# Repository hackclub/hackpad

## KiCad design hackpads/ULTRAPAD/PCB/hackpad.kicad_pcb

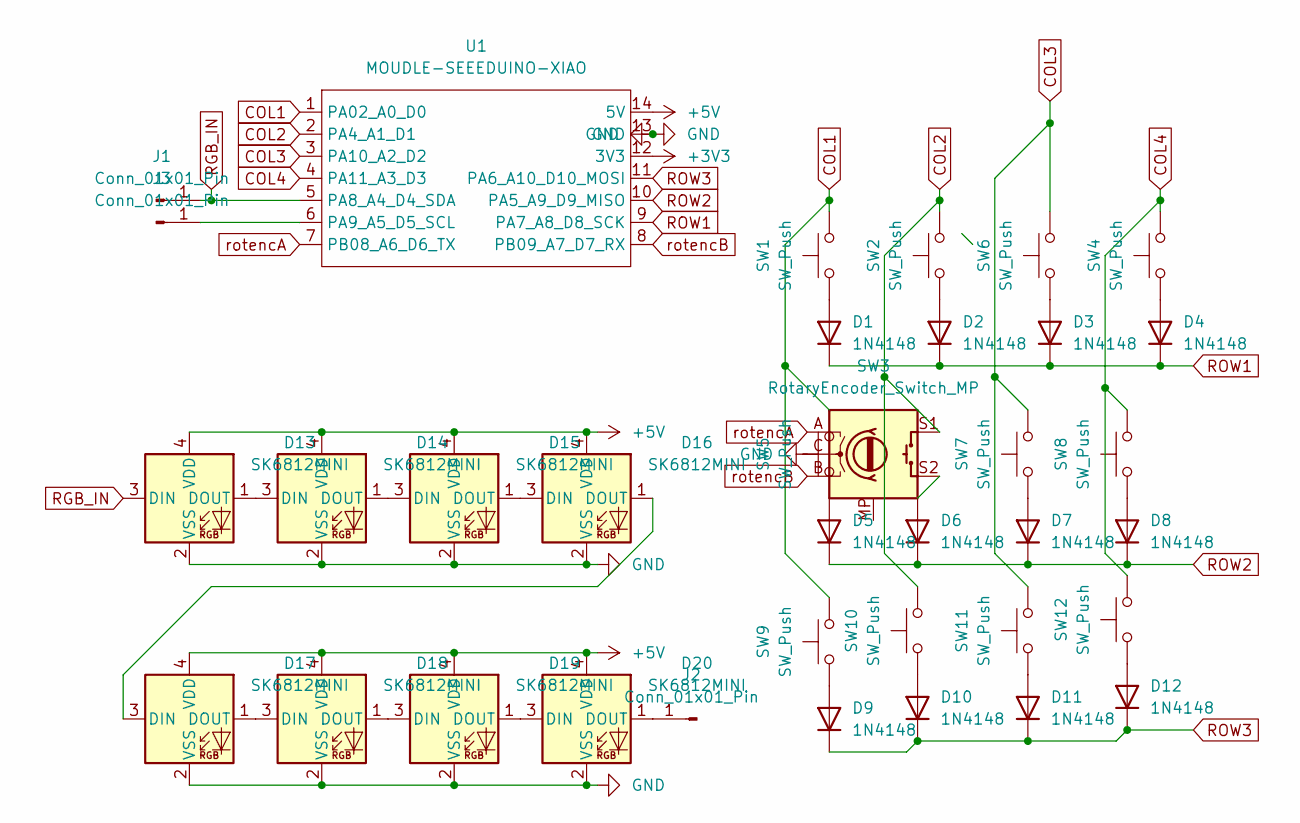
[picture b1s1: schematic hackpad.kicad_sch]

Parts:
D1, D2, D3, D4, D5, D6, D7, D8, D9, D10, D11, D12: 1N4148; D_DO-35_SOD27_P7.62mm_Horizontal
D13, D14, D15, D16, D17, D18, D19, D20: SK6812MINI; LED_SK6812MINI_PLCC4_3.5x3.5mm_P1.75mm
J1, J2, J3: Conn_01x01_Pin; PinHeader_1x01_P1.00mm_Vertical
SW1, SW2, SW4, SW5, SW6, SW7, SW8, SW9, SW10, SW11, SW12: SW_Push; SW_Cherry_MX_1.00u_PCB
SW3: RotaryEncoder_Switch_MP; RotaryEncoder_Alps_EC11E-Switch_Vertical_H20mm
U1: MOUDLE-SEEEDUINO-XIAO; XIAO-RP2040-DIP

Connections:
+3V3: U1.12 (3V3)
+5V: D13.4 (VDD), D14.4 (VDD), D15.4 (VDD), D16.4 (VDD), D17.4 (VDD), D18.4 (VDD), D19.4 (VDD), D20.4 (VDD), U1.14 (5V)
COL1: SW1.2, SW5.2, SW9.2, U1.1 (PA02_A0_D0)
COL2: SW2.2, SW3.S1, SW10.2, U1.2 (PA4_A1_D1)
COL3: SW6.2, SW7.2, SW11.2, U1.3 (PA10_A2_D2)
COL4: SW4.2, SW8.2, SW12.2, U1.4 (PA11_A3_D3)
GND: D13.2 (VSS), D14.2 (VSS), D15.2 (VSS), D16.2 (VSS), D17.2 (VSS), D18.2 (VSS), D19.2 (VSS), D20.2 (VSS), SW3.C, U1.13 (GND)
unnamed: D1.2 (A), SW1.1
unnamed: D2.2 (A), SW2.1
unnamed: D3.2 (A), SW6.1
unnamed: D4.2 (A), SW4.1
unnamed: D5.2 (A), SW5.1
unnamed: D6.2 (A), SW3.S2
unnamed: D7.2 (A), SW7.1
unnamed: D8.2 (A), SW8.1
unnamed: D9.2 (A), SW9.1
unnamed: D10.2 (A), SW10.1
unnamed: D11.2 (A), SW11.1
unnamed: D12.2 (A), SW12.1
unnamed: D13.1 (DOUT), D14.3 (DIN)
unnamed: D14.1 (DOUT), D15.3 (DIN)
unnamed: D15.1 (DOUT), D16.3 (DIN)
unnamed: D16.1 (DOUT), D17.3 (DIN)
unnamed: D17.1 (DOUT), D18.3 (DIN)
unnamed: D18.1 (DOUT), D19.3 (DIN)
unnamed: D19.1 (DOUT), D20.3 (DIN)
unnamed: D20.1 (DOUT), J2.1
unnamed: J3.1, U1.6 (PA9_A5_D5_SCL)
RGB_IN: D13.3 (DIN), J1.1, U1.5 (PA8_A4_D4_SDA)
ROW1: D1.1 (K), D2.1 (K), D3.1 (K), D4.1 (K), U1.9 (PA7_A8_D8_SCK)
ROW2: D5.1 (K), D6.1 (K), D7.1 (K), D8.1 (K), U1.10 (PA5_A9_D9_MISO)
ROW3: D9.1 (K), D10.1 (K), D11.1 (K), D12.1 (K), U1.11 (PA6_A10_D10_MOSI)
rotencA: SW3.A, U1.7 (PB08_A6_D6_TX)
rotencB: SW3.B, U1.8 (PB09_A7_D7_RX)

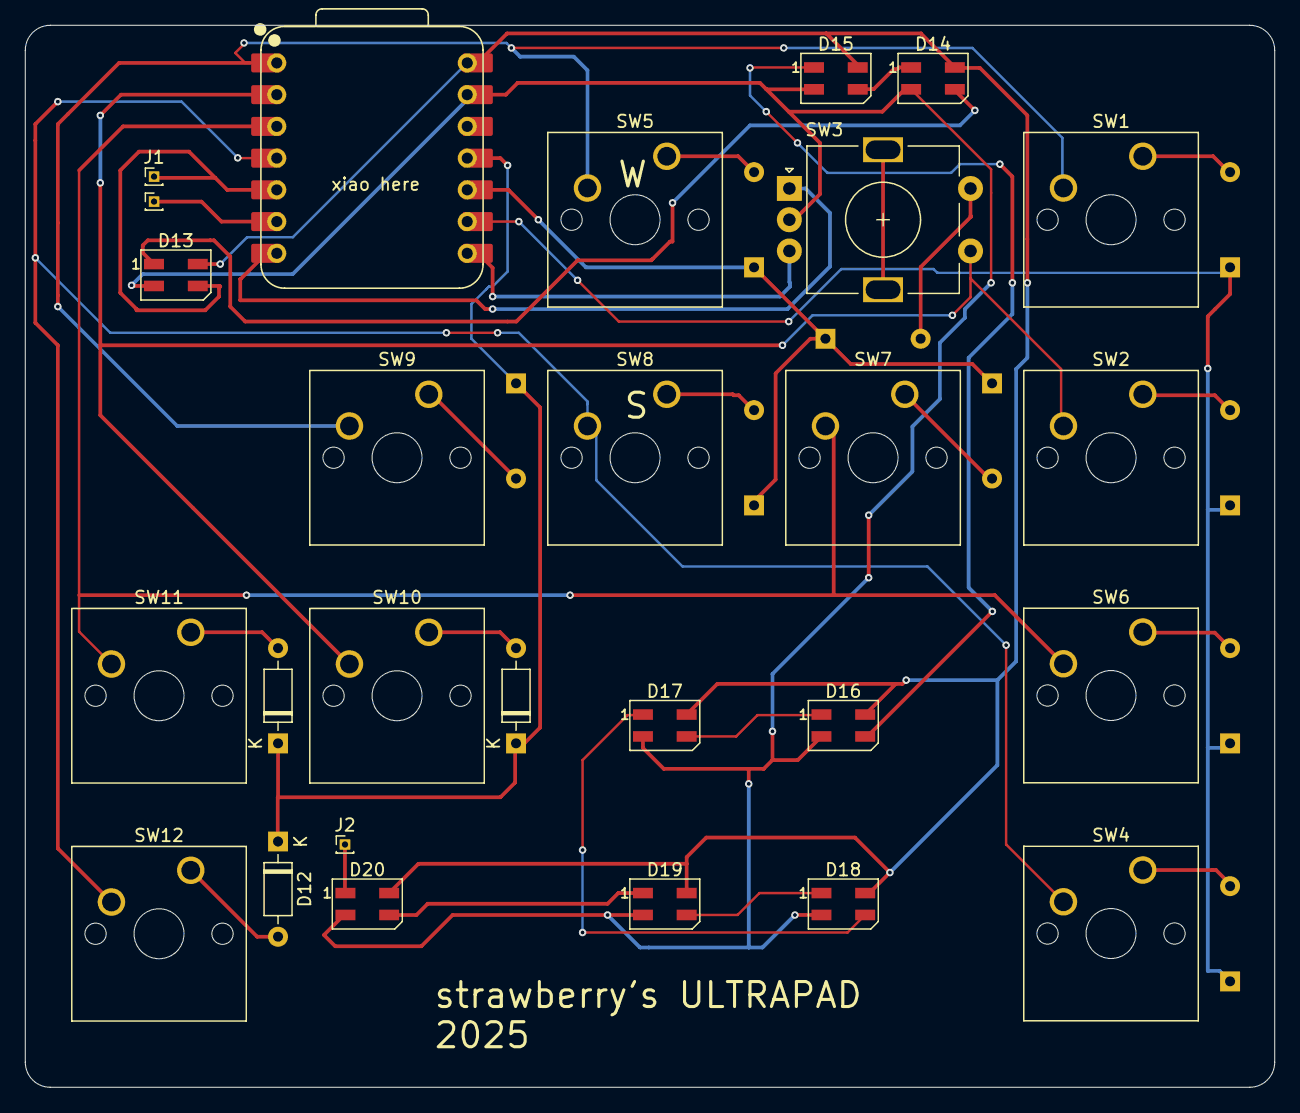
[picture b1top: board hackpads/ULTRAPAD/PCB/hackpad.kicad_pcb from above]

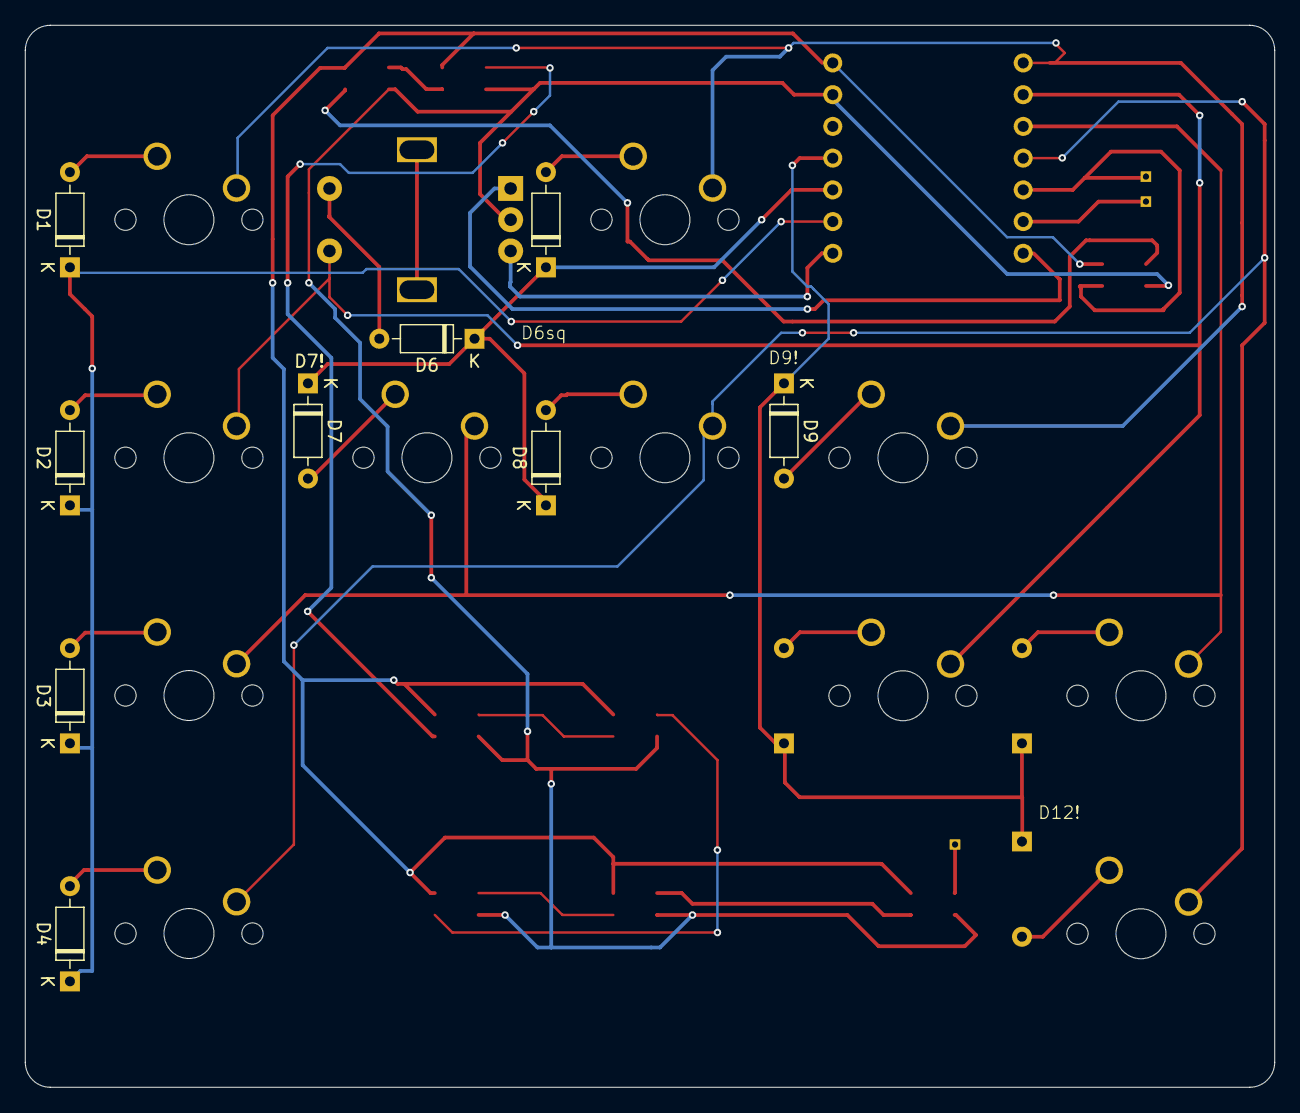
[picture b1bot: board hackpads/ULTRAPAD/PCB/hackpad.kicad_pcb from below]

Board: 2 copper layers, 100.0 x 85.0 mm, 36 parts (9 on the bottom side), 33 nets.

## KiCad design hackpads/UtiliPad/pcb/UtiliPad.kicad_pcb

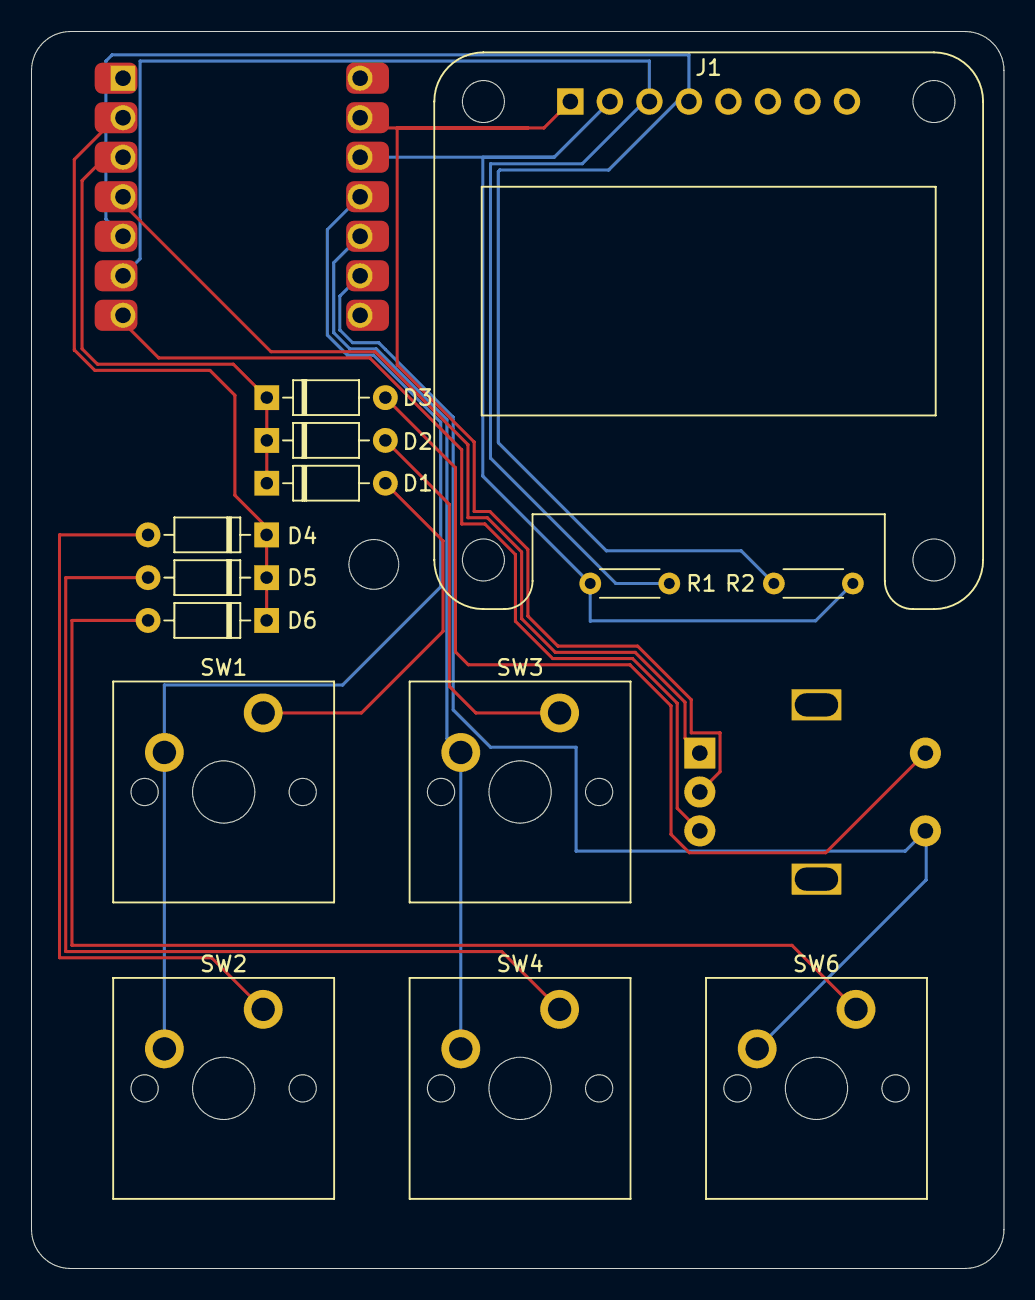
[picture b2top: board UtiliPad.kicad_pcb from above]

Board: 2 copper layers, 62.5 x 79.5 mm, 16 parts (0 on the bottom side), 17 nets.

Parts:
D1, D2, D3, D4, D5, D6: 1N4148; D_DO-35_SOD27_P7.62mm_Horizontal
J1: 0.96" OLED Display; Adafruit_SSD1306
R1, R2: 4.7k; R_Axial_DIN0204_L3.6mm_D1.6mm_P5.08mm_Horizontal
SW1, SW2, SW3, SW4, SW6: MX; MX_PCB_1.00u
SW7: RotaryEncoder_Switch; Encoder_EC11_MX
U1: MCU_Seeed_XIAO_RP2040; Seeed_XIAO_RP2040

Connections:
+3.3V: J1.2, R1.2, R2.2, U1.12 (3V3)
COL0: SW1.1, SW2.1, U1.11 (PA6_A10_D10_MOSI)
COL1: SW3.1, SW4.1, U1.10 (PA5_A9_D9_MISO)
COL2: SW6.1, SW7.S1, U1.9 (PA7_A8_D8_SCK)
GND: J1.1, SW7.C, U1.13 (GND)
unnamed: D1.2 (A), SW1.2
unnamed: D2.2 (A), SW3.2
unnamed: D4.2 (A), SW2.2
unnamed: D5.2 (A), SW4.2
unnamed: D6.2 (A), SW6.2
R1_A: SW7.A, U1.4 (PA11_A3_D3)
R1_B: SW7.B, U1.7 (PB08_A6_D6_TX)
R1_G: D3.2 (A), SW7.S2
ROW0: D1.1 (K), D2.1 (K), D3.1 (K), U1.3 (PA10_A2_D2)
ROW1: D4.1 (K), D5.1 (K), D6.1 (K), U1.2 (PA4_A1_D1)
SCL: J1.3, R1.1, U1.6 (PA9_A5_D5_SCL)
SDA: J1.4, R2.1, U1.5 (PA8_A4_D4_SDA)

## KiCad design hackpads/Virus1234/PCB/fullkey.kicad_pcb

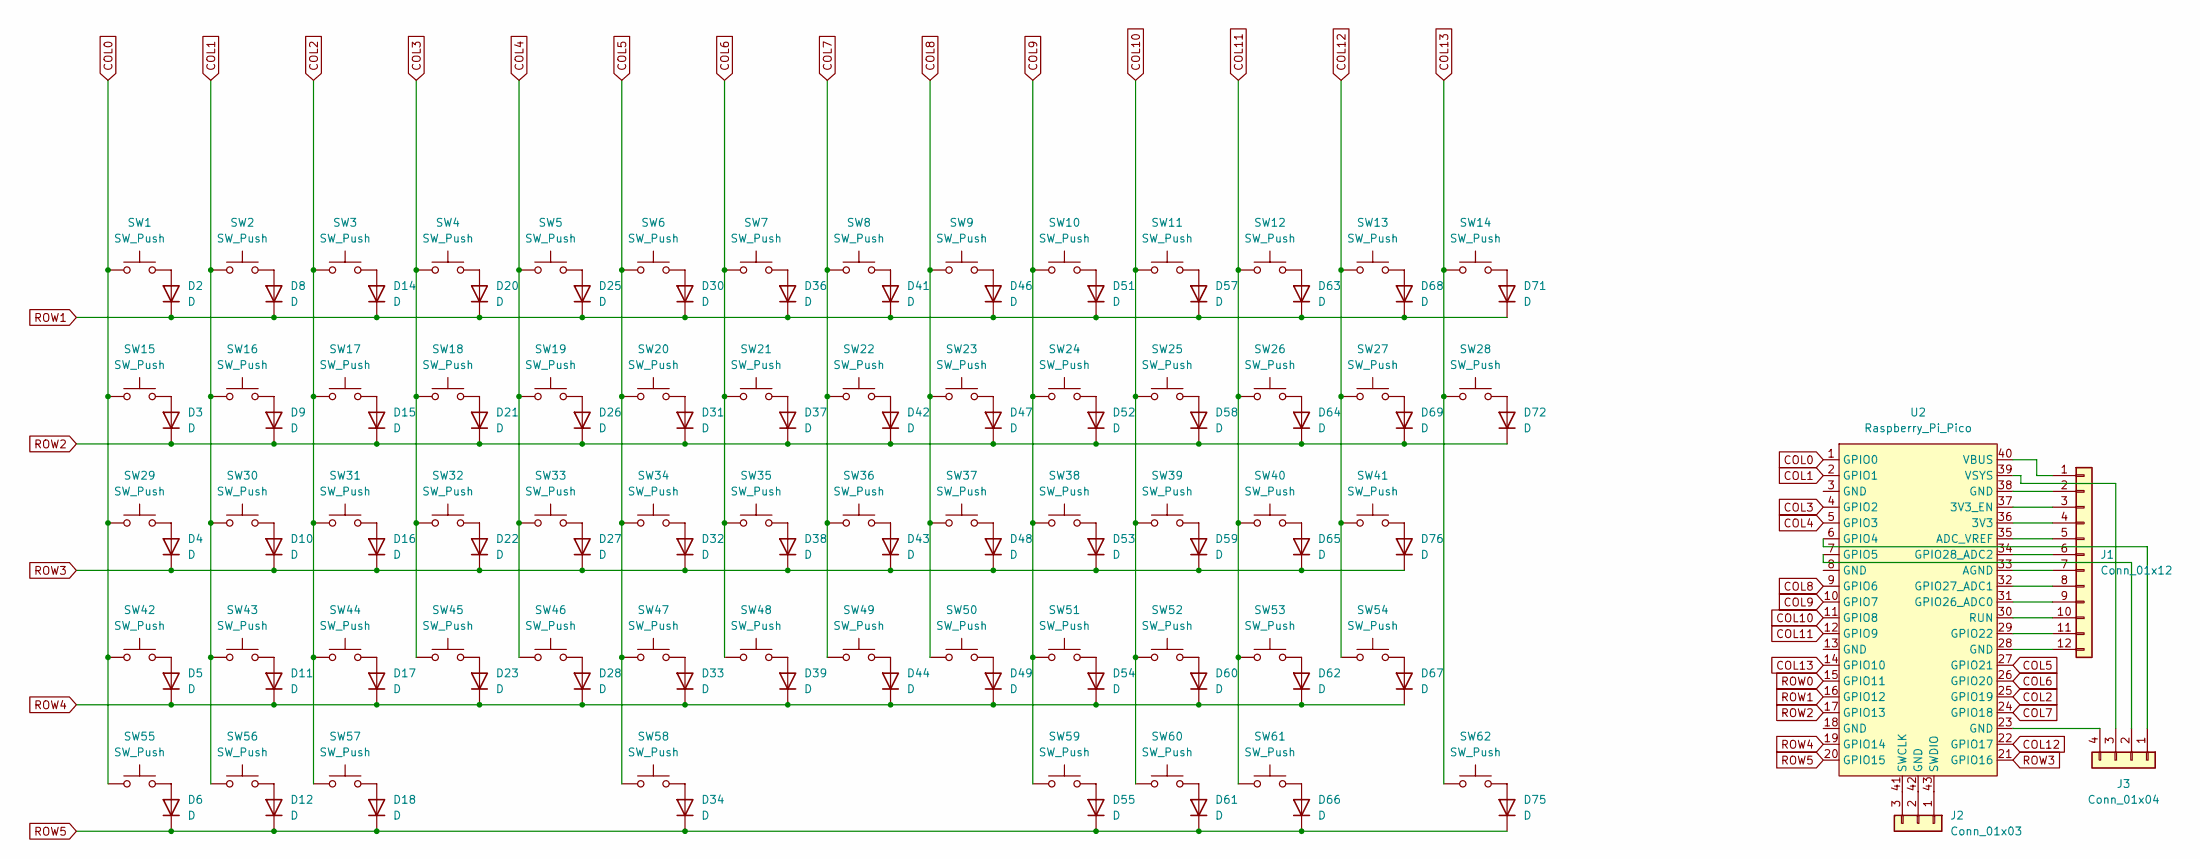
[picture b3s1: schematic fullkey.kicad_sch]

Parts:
D2, D3, D4, D5, D6, D8, D9, D10, D11, D12, D14, D15, D16, D17, D18, D20, D21, D22, D23, D25, D26, D27, D28, D30, D31, D32, D33, D34, D36, D37, D38, D39, D41, D42, D43, D44, D46, D47, D48, D49, D51, D52, D53, D54, D55, D57, D58, D59, D60, D61, D62, D63, D64, D65, D66, D67, D68, D69, D71, D72, D75, D76: D; D_DO-41_SOD81_P12.70mm_Horizontal
J1: Conn_01x12; PinHeader_1x12_P2.54mm_Horizontal
J2: Conn_01x03; PinHeader_1x03_P2.54mm_Horizontal
J3: Conn_01x04; PinHeader_1x04_P2.54mm_Vertical
SW1, SW2, SW3, SW4, SW5, SW6, SW7, SW8, SW9, SW10, SW11, SW12, SW13, SW14, SW15, SW16, SW17, SW18, SW19, SW20, SW21, SW22, SW23, SW24, SW25, SW26, SW27, SW28, SW29, SW30, SW31, SW32, SW33, SW34, SW35, SW36, SW37, SW38, SW39, SW40, SW41, SW42, SW43, SW44, SW45, SW46, SW47, SW48, SW49, SW50, SW51, SW52, SW53, SW54, SW55, SW56, SW57, SW58, SW59, SW60, SW61, SW62: SW_Push; MX_PCB_1.00u
U2: Raspberry_Pi_Pico

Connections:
COL0: SW1.1, SW15.1, SW29.1, SW42.1, SW55.1, U2.1 (GPIO0)
COL1: SW2.1, SW16.1, SW30.1, SW43.1, SW56.1, U2.2 (GPIO1)
COL2: SW3.1, SW17.1, SW31.1, SW44.1, SW57.1, U2.25 (GPIO19)
COL3: SW4.1, SW18.1, SW32.1, SW45.1, U2.4 (GPIO2)
COL4: SW5.1, SW19.1, SW33.1, SW46.1, U2.5 (GPIO3)
COL5: SW6.1, SW20.1, SW34.1, SW47.1, SW58.1, U2.27 (GPIO21)
COL6: SW7.1, SW21.1, SW35.1, SW48.1, U2.26 (GPIO20)
COL7: SW8.1, SW22.1, SW36.1, SW49.1, U2.24 (GPIO18)
COL8: SW9.1, SW23.1, SW37.1, SW50.1, U2.9 (GPIO6)
COL9: SW10.1, SW24.1, SW38.1, SW51.1, SW59.1, U2.10 (GPIO7)
COL10: SW11.1, SW25.1, SW39.1, SW52.1, SW60.1, U2.11 (GPIO8)
COL11: SW12.1, SW26.1, SW40.1, SW53.1, SW61.1, U2.12 (GPIO9)
COL12: SW13.1, SW27.1, SW41.1, SW54.1, U2.22 (GPIO17)
COL13: SW14.1, SW28.1, SW62.1, U2.14 (GPIO10)
unnamed: D2.2 (A), SW1.2
unnamed: D3.2 (A), SW15.2
unnamed: D4.2 (A), SW29.2
unnamed: D5.2 (A), SW42.2
unnamed: D6.2 (A), SW55.2
unnamed: D8.2 (A), SW2.2
unnamed: D9.2 (A), SW16.2
unnamed: D10.2 (A), SW30.2
unnamed: D11.2 (A), SW43.2
unnamed: D12.2 (A), SW56.2
unnamed: D14.2 (A), SW3.2
unnamed: D15.2 (A), SW17.2
unnamed: D16.2 (A), SW31.2
unnamed: D17.2 (A), SW44.2
unnamed: D18.2 (A), SW57.2
unnamed: D20.2 (A), SW4.2
unnamed: D21.2 (A), SW18.2
unnamed: D22.2 (A), SW32.2
unnamed: D23.2 (A), SW45.2
unnamed: D25.2 (A), SW5.2
unnamed: D26.2 (A), SW19.2
unnamed: D27.2 (A), SW33.2
unnamed: D28.2 (A), SW46.2
unnamed: D30.2 (A), SW6.2
unnamed: D31.2 (A), SW20.2
unnamed: D32.2 (A), SW34.2
unnamed: D33.2 (A), SW47.2
unnamed: D34.2 (A), SW58.2
unnamed: D36.2 (A), SW7.2
unnamed: D37.2 (A), SW21.2
unnamed: D38.2 (A), SW35.2
unnamed: D39.2 (A), SW48.2
unnamed: D41.2 (A), SW8.2
unnamed: D42.2 (A), SW22.2
unnamed: D43.2 (A), SW36.2
unnamed: D44.2 (A), SW49.2
unnamed: D46.2 (A), SW9.2
unnamed: D47.2 (A), SW23.2
unnamed: D48.2 (A), SW37.2
unnamed: D49.2 (A), SW50.2
unnamed: D51.2 (A), SW10.2
unnamed: D52.2 (A), SW24.2
unnamed: D53.2 (A), SW38.2
unnamed: D54.2 (A), SW51.2
unnamed: D55.2 (A), SW59.2
unnamed: D57.2 (A), SW11.2
unnamed: D58.2 (A), SW25.2
unnamed: D59.2 (A), SW39.2
unnamed: D60.2 (A), SW52.2
unnamed: D61.2 (A), SW60.2
unnamed: D62.2 (A), SW53.2
unnamed: D63.2 (A), SW12.2
unnamed: D64.2 (A), SW26.2
unnamed: D65.2 (A), SW40.2
unnamed: D66.2 (A), SW61.2
unnamed: D67.2 (A), SW54.2
unnamed: D68.2 (A), SW13.2
unnamed: D69.2 (A), SW27.2
unnamed: D71.2 (A), SW14.2
unnamed: D72.2 (A), SW28.2
unnamed: D75.2 (A), SW62.2
unnamed: D76.2 (A), SW41.2
unnamed: J1.1, U2.40 (VBUS)
unnamed: J1.2, U2.38 (GND)
unnamed: J1.3, U2.37 (3V3_EN)
unnamed: J1.4, U2.36 (3V3)
unnamed: J1.5, U2.35 (ADC_VREF)
unnamed: J1.6, U2.34 (GPIO28_ADC2)
unnamed: J1.7, U2.33 (AGND)
unnamed: J1.8, U2.32 (GPIO27_ADC1)
unnamed: J1.9, U2.31 (GPIO26_ADC0)
unnamed: J1.10, U2.30 (RUN)
unnamed: J1.11, U2.29 (GPIO22)
unnamed: J1.12, U2.28 (GND)
unnamed: J2.1, U2.43 (SWDIO)
unnamed: J2.2, U2.42 (GND)
unnamed: J2.3, U2.41 (SWCLK)
unnamed: J3.1, U2.6 (GPIO4)
unnamed: J3.2, U2.7 (GPIO5)
unnamed: J3.3, U2.39 (VSYS)
unnamed: J3.4, U2.23 (GND)
ROW0: U2.15 (GPIO11)
ROW1: D2.1 (K), D8.1 (K), D14.1 (K), D20.1 (K), D25.1 (K), D30.1 (K), D36.1 (K), D41.1 (K), D46.1 (K), D51.1 (K), D57.1 (K), D63.1 (K), D68.1 (K), D71.1 (K), U2.16 (GPIO12)
ROW2: D3.1 (K), D9.1 (K), D15.1 (K), D21.1 (K), D26.1 (K), D31.1 (K), D37.1 (K), D42.1 (K), D47.1 (K), D52.1 (K), D58.1 (K), D64.1 (K), D69.1 (K), D72.1 (K), U2.17 (GPIO13)
ROW3: D4.1 (K), D10.1 (K), D16.1 (K), D22.1 (K), D27.1 (K), D32.1 (K), D38.1 (K), D43.1 (K), D48.1 (K), D53.1 (K), D59.1 (K), D65.1 (K), D76.1 (K), U2.21 (GPIO16)
ROW4: D5.1 (K), D11.1 (K), D17.1 (K), D23.1 (K), D28.1 (K), D33.1 (K), D39.1 (K), D44.1 (K), D49.1 (K), D54.1 (K), D60.1 (K), D62.1 (K), D67.1 (K), U2.19 (GPIO14)
ROW5: D6.1 (K), D12.1 (K), D18.1 (K), D34.1 (K), D55.1 (K), D61.1 (K), D66.1 (K), D75.1 (K), U2.20 (GPIO15)

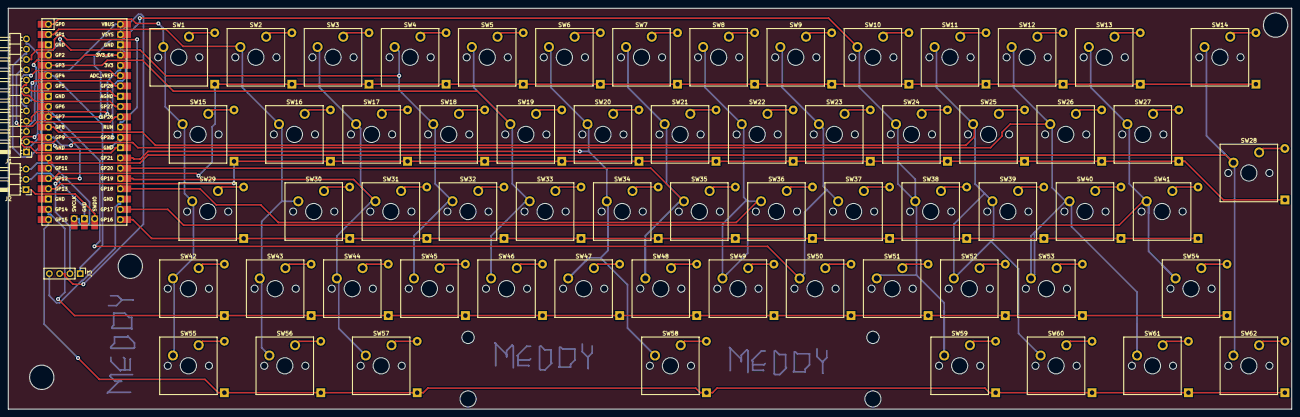
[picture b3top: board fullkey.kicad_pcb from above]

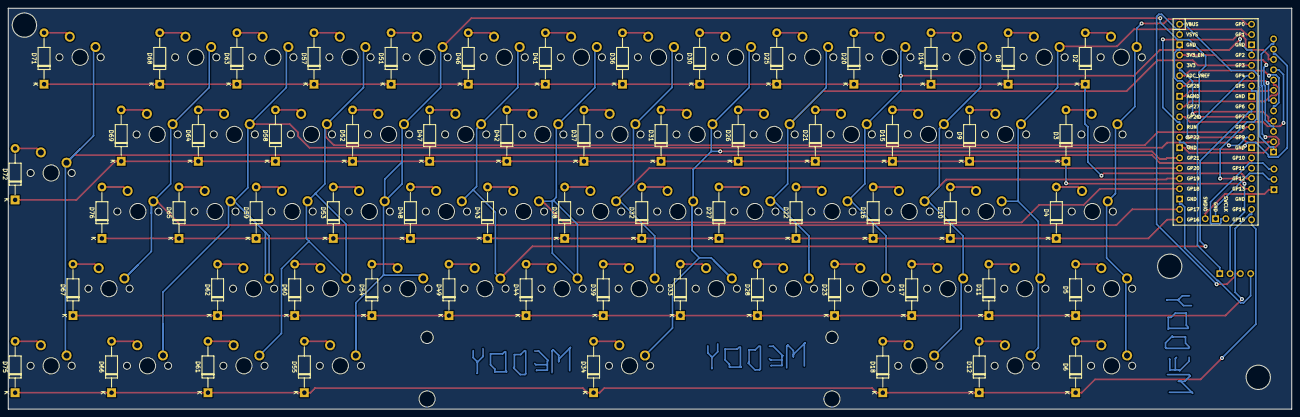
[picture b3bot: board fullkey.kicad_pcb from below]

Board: 2 copper layers, 317.0 x 99.0 mm, 128 parts (62 on the bottom side), 100 nets.

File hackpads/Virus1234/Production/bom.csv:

Designator,Footprint,Quantity,Value,LCSC Part #
"D10, D11, D12, D14, D15, D16, D17, D18, D2, D20, D21, D22, D23, D25, D26, D27, D28, D3, D30, D31, D32, D33, D34, D36, D37, D38, D39, D4, D41, D42, D43, D44, D46, D47, D48, D49, D5, D51, D52, D53, D54, D55, D57, D58, D59, D6, D60, D61, D62, D63, D64, D65, D66, D67, D68, D69, D71, D72, D75, D76, D8, D9",D_DO-41_SOD81_P12.70mm_Horizontal,62,D,
J1,PinHeader_1x12_P2.54mm_Horizontal,1,Conn_01x12,
J2,PinHeader_1x03_P2.54mm_Horizontal,1,Conn_01x03,
J3,PinHeader_1x04_P2.54mm_Vertical,1,Conn_01x04,
"SW1, SW10, SW11, SW12, SW13, SW14, SW15, SW16, SW17, SW18, SW19, SW2, SW20, SW21, SW22, SW23, SW24, SW25, SW26, SW27, SW28, SW29, SW3, SW30, SW31, SW32, SW33, SW34, SW35, SW36, SW37, SW38, SW39, SW4, SW40, SW41, SW42, SW43, SW44, SW45, SW46, SW47, SW48, SW49, SW5, SW50, SW51, SW52, SW53, SW54, SW55, SW56, SW57, SW58, SW59, SW6, SW60, SW61, SW62, SW7, SW8, SW9",MX_PCB_1.00u,62,SW_Push,
U2,Raspberry_Pi_Pico,1,Raspberry_Pi_Pico,

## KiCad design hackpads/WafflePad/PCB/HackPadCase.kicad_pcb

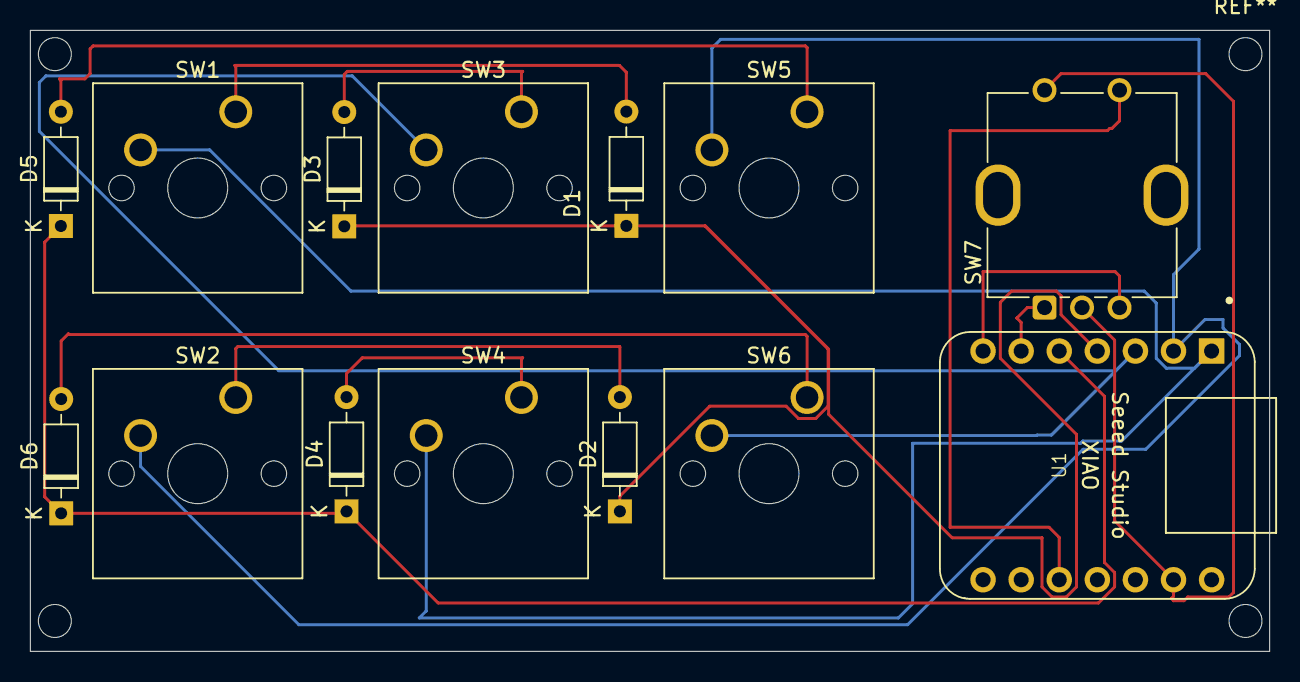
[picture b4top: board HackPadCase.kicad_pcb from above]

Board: 2 copper layers, 82.6 x 41.4 mm, 14 parts (0 on the bottom side), 15 nets.

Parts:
D1, D2, D3, D4, D5, D6: 1N4148; D_DO-35_SOD27_P7.62mm_Horizontal
SW1, SW2, SW3, SW4, SW5, SW6: SW_Push; SW_Cherry_MX_1.00u_PCB
SW7: RotaryEncoder_Switch; RotaryEncoder_Bourns_Vertical_PEC12R-3x17F-Sxxxx
U1: Seeed Studio XIAO SAMD21; XIAO-Generic-Thruhole-14P-2.54-21X17.8MM

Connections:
Column 1: SW1.2, SW4.2, U1.1 (PA02_A0_D0)
Column 2: SW2.2, SW5.2, U1.2 (PA4_A1_D1)
Column 3: SW3.2, SW6.2, U1.3 (PA10_A2_D2)
GND: SW7.C, SW7.S1, U1.13 (GND)
unnamed: D1.2 (A), SW1.1
unnamed: D2.2 (A), SW2.1
unnamed: D3.2 (A), SW3.1
unnamed: D4.2 (A), SW4.1
unnamed: D5.2 (A), SW5.1
unnamed: D6.2 (A), SW6.1
unnamed: SW7.S2, U1.10 (PA5_A9_D9_MISO)
unnamed: SW7.A, U1.6 (PA9_A5_D5_SCL)
unnamed: SW7.B, U1.7 (PB08_A6_D6_TX)
Row 1: D1.1 (K), D2.1 (K), D3.1 (K), U1.4 (PA11_A3_D3)
Row 2: D4.1 (K), D5.1 (K), D6.1 (K), U1.5 (PA8_A4_D4_SDA)

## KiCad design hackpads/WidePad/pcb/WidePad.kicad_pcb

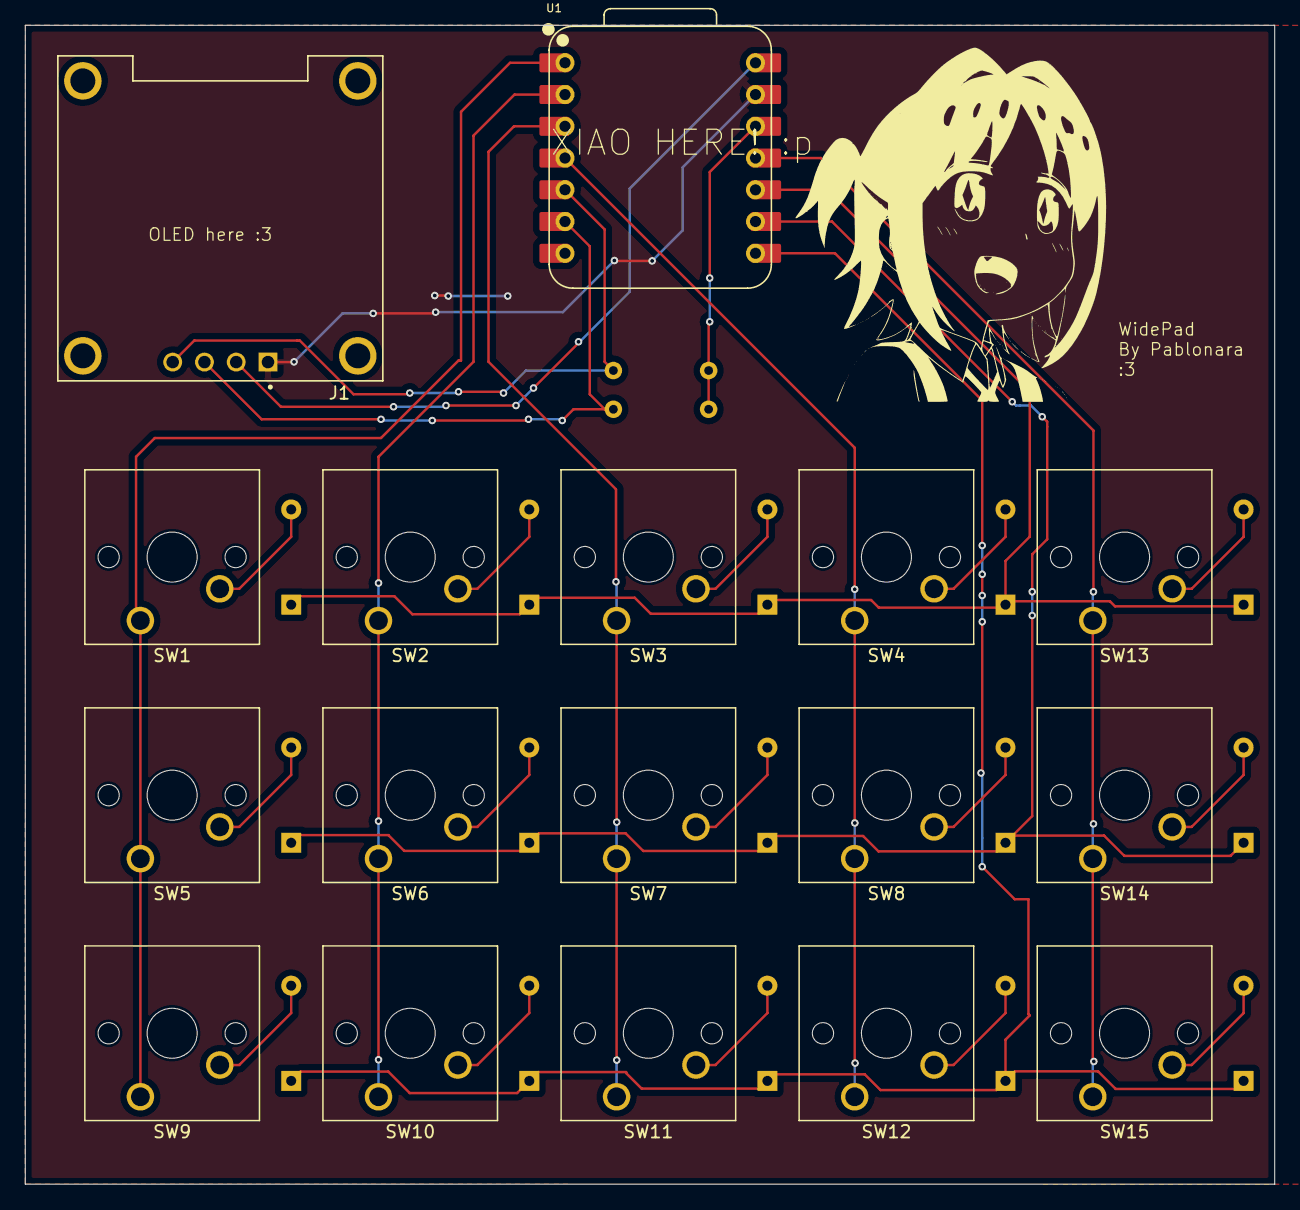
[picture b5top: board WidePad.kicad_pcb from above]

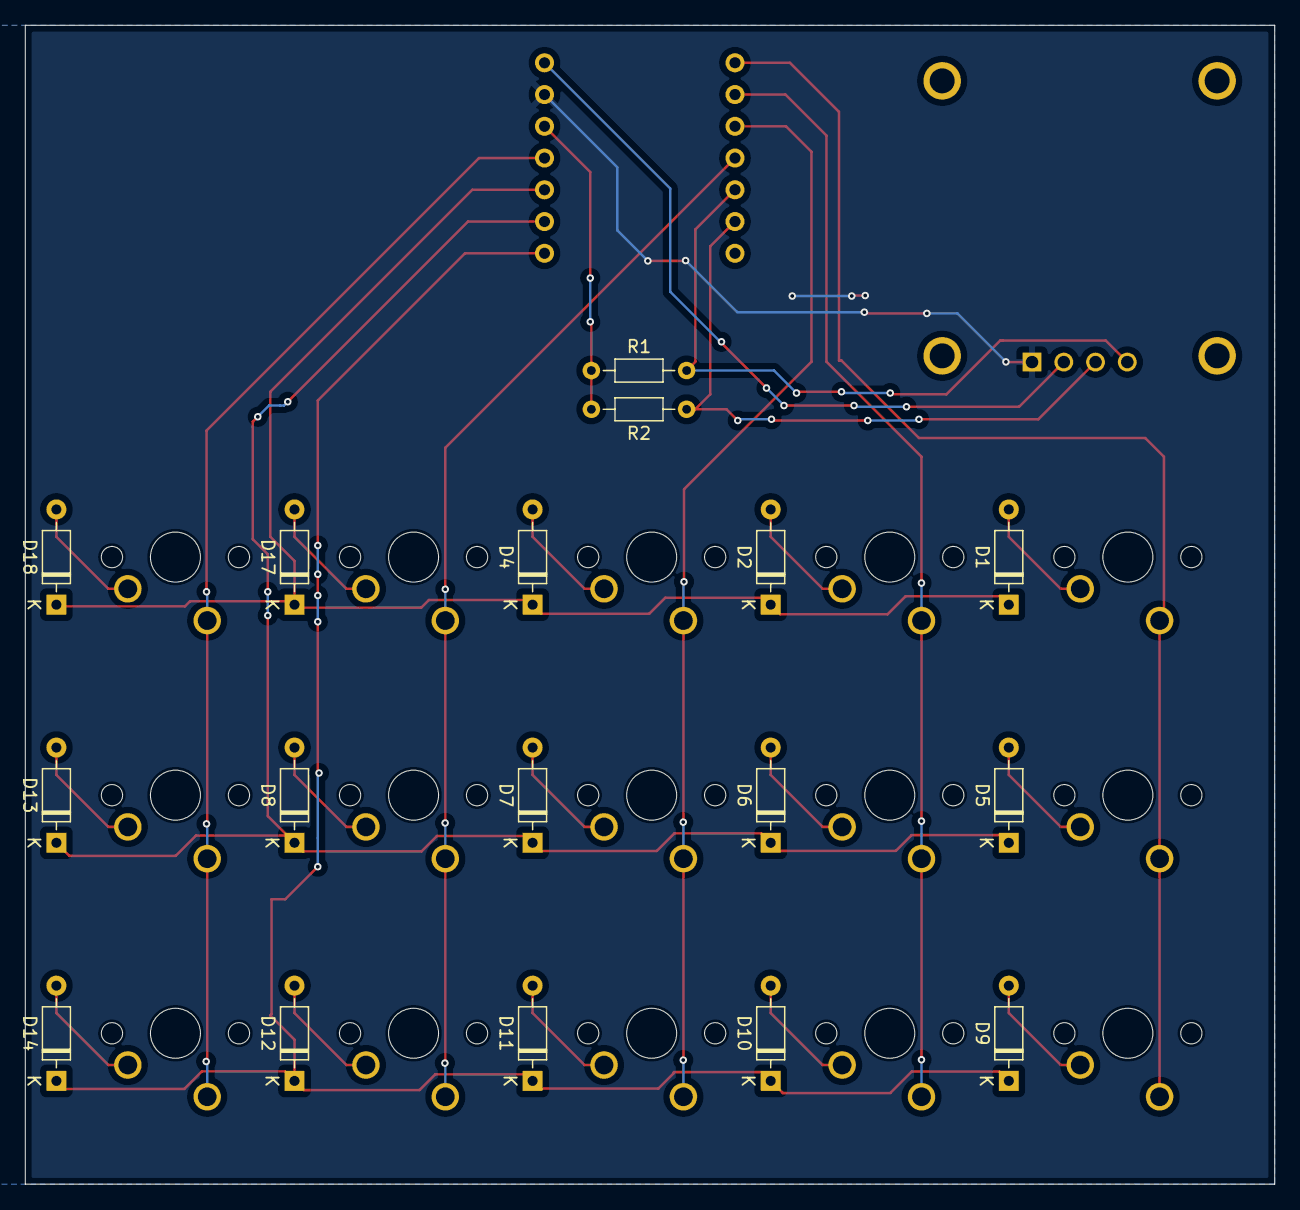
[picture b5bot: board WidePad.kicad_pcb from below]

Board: 2 copper layers, 100.0 x 92.7 mm, 34 parts (17 on the bottom side), 28 nets.

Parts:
D1, D2, D4, D5, D6, D7, D8, D9, D10, D11, D12, D13, D14, D17, D18: D; D_DO-35_SOD27_P7.62mm_Horizontal
J1: Conn_01x04_Pin; MODULE_DM-OLED096-636
R1, R2: R; R_Axial_DIN0204_L3.6mm_D1.6mm_P7.62mm_Horizontal
SW1, SW2, SW3, SW4, SW5, SW6, SW7, SW8, SW9, SW10, SW11, SW12, SW13, SW14, SW15: SW_Push; SW_Cherry_MX_1.00u_PCB
U1: XIAO-RP2040-DIP

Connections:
+3.3V: R1.1, R2.2, U1.12 (3V3)
+5V: J1.2, U1.14 (VBUS)
GND: J1.1, U1.13 (GND)
unnamed: D1.2 (A), SW1.2
unnamed: D1.1 (K), D2.1 (K), D4.1 (K), D17.1 (K), D18.1 (K), U1.10 (GPIO4/MISO)
unnamed: D2.2 (A), SW2.2
unnamed: D4.2 (A), SW3.2
unnamed: D5.2 (A), SW5.2
unnamed: D6.2 (A), SW6.2
unnamed: D7.2 (A), SW7.2
unnamed: D8.2 (A), SW8.2
unnamed: D9.2 (A), SW9.2
unnamed: D10.2 (A), SW10.2
unnamed: D9.1 (K), D10.1 (K), D11.1 (K), D12.1 (K), D14.1 (K), U1.8 (GPIO1/RX)
unnamed: D11.2 (A), SW11.2
unnamed: D12.2 (A), SW12.2
unnamed: D13.2 (A), SW14.2
unnamed: D5.1 (K), D6.1 (K), D7.1 (K), D8.1 (K), D13.1 (K), U1.9 (GPIO2/SCK)
unnamed: D14.2 (A), SW15.2
unnamed: D17.2 (A), SW4.2
unnamed: D18.2 (A), SW13.2
unnamed: SW13.1, SW14.1, SW15.1, U1.11 (GPIO3/MOSI)
unnamed: J1.4, R1.2, U1.5 (GPIO6/SDA)
unnamed: J1.3, R2.1, U1.6 (GPIO7/SCL)
unnamed: SW1.1, SW5.1, SW9.1, U1.1 (GPIO26/ADC0/A0)
unnamed: SW2.1, SW6.1, SW10.1, U1.2 (GPIO27/ADC1/A1)
unnamed: SW3.1, SW7.1, SW11.1, U1.3 (GPIO28/ADC2/A2)
unnamed: SW4.1, SW8.1, SW12.1, U1.4 (GPIO29/ADC3/A3)

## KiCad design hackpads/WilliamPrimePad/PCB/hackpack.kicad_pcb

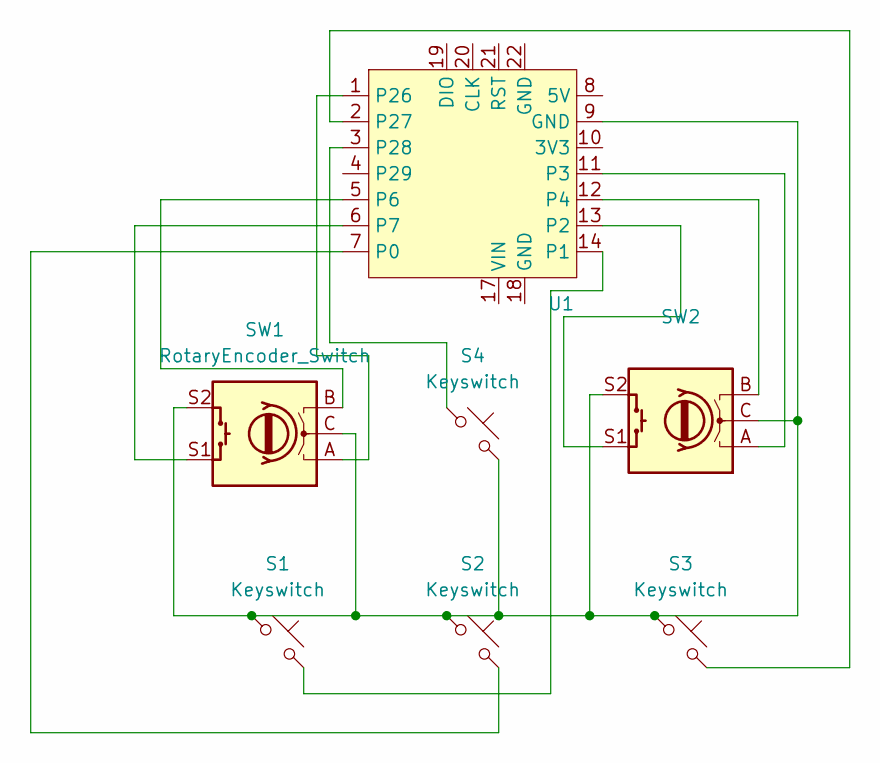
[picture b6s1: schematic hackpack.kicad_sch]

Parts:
S1, S2, S3, S4: Keyswitch; MX_PCB
SW1, SW2: RotaryEncoder_Switch; Encoder_EC11_MX
U1: Seeeduino Xiao rp2040; Xiao_rp2040_ACH

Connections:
unnamed: S1.1, S2.1, S3.1, S4.2, SW1.C, SW1.S2, SW2.C, SW2.S2, U1.9 (GND)
unnamed: S2.2, U1.7 (P0)
unnamed: S1.2, U1.14 (P1)
unnamed: SW2.S1, U1.13 (P2)
unnamed: SW2.A, U1.11 (P3)
unnamed: SW2.B, U1.12 (P4)
unnamed: SW1.B, U1.5 (P6)
unnamed: SW1.S1, U1.6 (P7)
unnamed: SW1.A, U1.1 (P26)
unnamed: S3.2, U1.2 (P27)
unnamed: S4.1, U1.3 (P28)

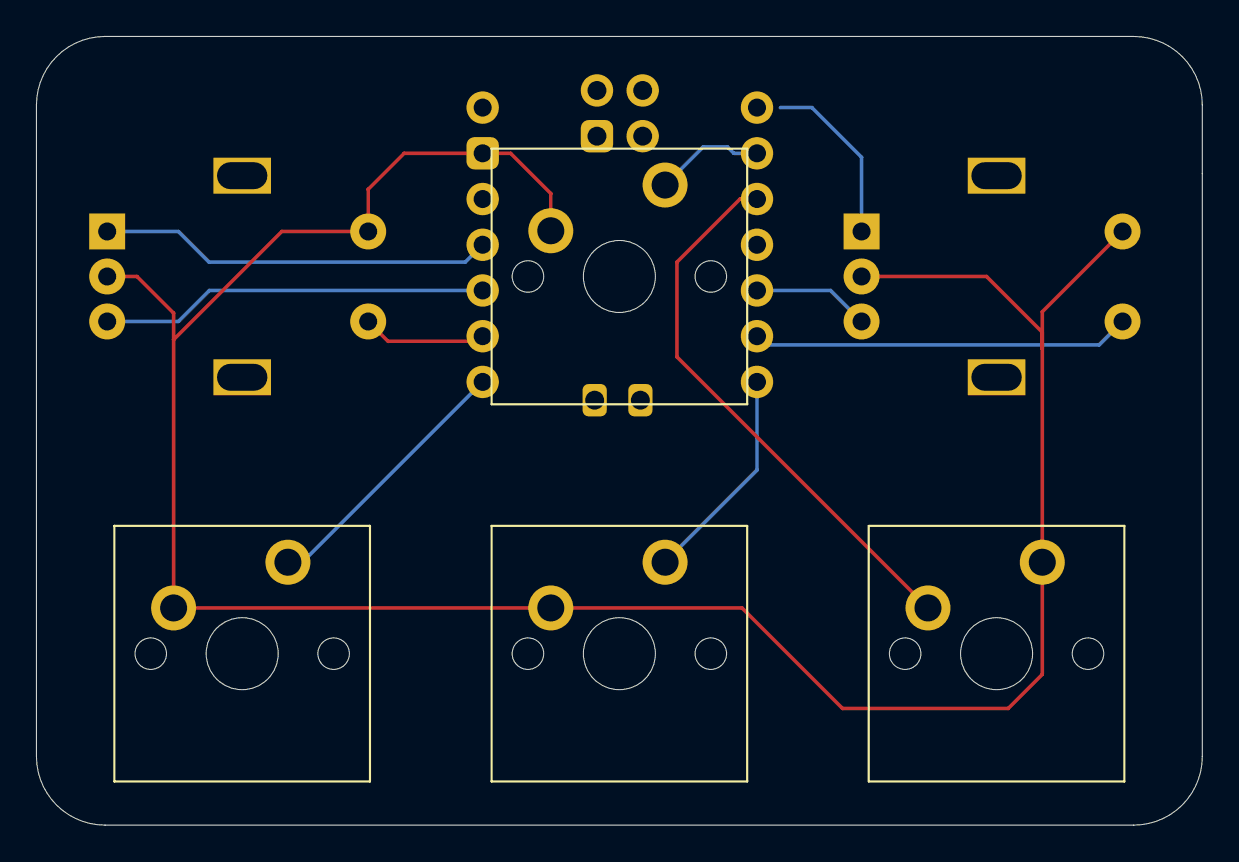
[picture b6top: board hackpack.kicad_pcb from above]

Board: 2 copper layers, 64.8 x 43.8 mm, 7 parts (1 on the bottom side), 11 nets.

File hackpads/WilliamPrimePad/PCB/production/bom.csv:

Designator,Footprint,Quantity,Value,LCSC Part #
"S1, S2, S3, S4",MX_PCB,4,Keyswitch,
"SW1, SW2",Encoder_EC11_MX,2,RotaryEncoder_Switch,

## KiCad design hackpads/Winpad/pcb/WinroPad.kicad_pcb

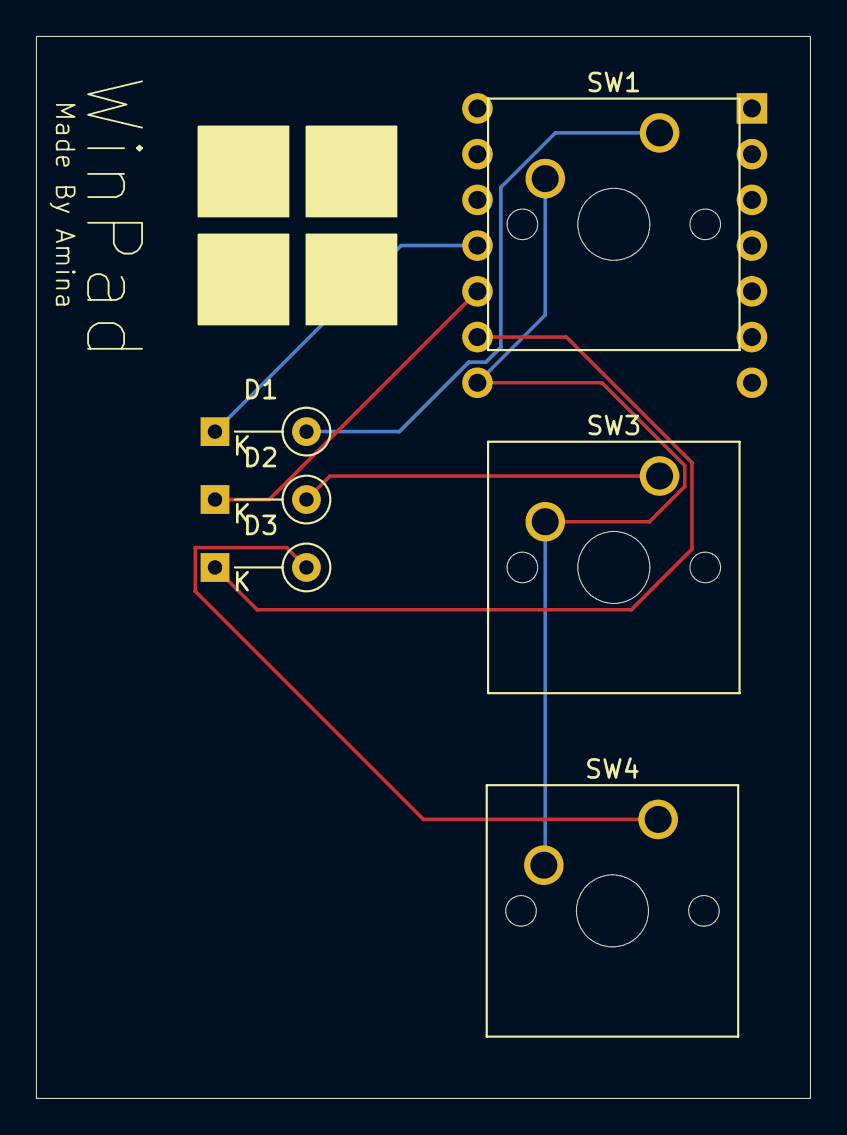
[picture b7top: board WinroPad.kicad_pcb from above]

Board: 2 copper layers, 43.0 x 59.0 mm, 7 parts (1 on the bottom side), 7 nets.

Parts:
D1, D2, D3: D; D_DO-35_SOD27_P5.08mm_Vertical_KathodeUp
SW1, SW3, SW4: SW_Push; SW_Cherry_MX_1.00u_PCB
U1: Seeed Studio XIAO SAMD21; XIAO-Generic-Thruhole-14P-2.54-21X17.8MM

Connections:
unnamed: D1.2 (A), SW1.1
unnamed: D1.1 (K), U1.11 (PA6_A10_D10_MOSI)
unnamed: D2.2 (A), SW3.1
unnamed: D2.1 (K), U1.10 (PA5_A9_D9_MISO)
unnamed: D3.2 (A), SW4.1
unnamed: D3.1 (K), U1.9 (PA7_A8_D8_SCK)
unnamed: SW1.2, SW3.2, SW4.2, U1.8 (PB09_A7_D7_RX)
